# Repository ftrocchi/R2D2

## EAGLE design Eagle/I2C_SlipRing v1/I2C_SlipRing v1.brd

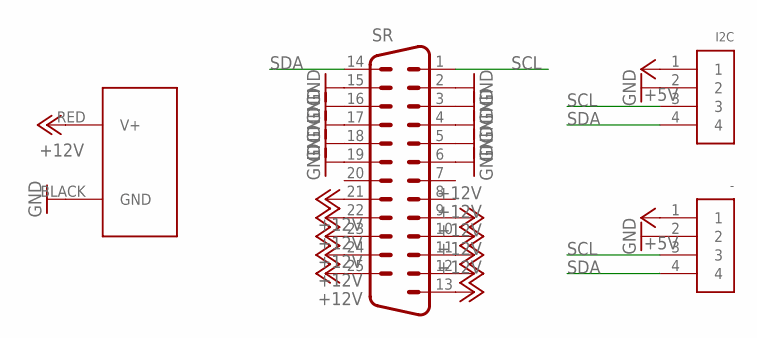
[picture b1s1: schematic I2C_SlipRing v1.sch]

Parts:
-: 1X4-CLEANBIG; 1X04-CLEANBIG
I2C: 1X4-CLEANBIG; 1X04-CLEANBIG
J1: POWERPOLE_POWER25A_HORIZONTAL_G2; POWERPOLE_PAIR_25A_HORIZ_G2
SR: DB25HP; M25HP

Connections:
+5V: -.1, I2C.1
+12V: J1.RED (V+), SR.9, SR.10, SR.11, SR.12, SR.13, SR.21, SR.22, SR.23, SR.24, SR.25
GND: -.2, I2C.2, J1.BLACK (GND), SR.2, SR.3, SR.4, SR.5, SR.6, SR.15, SR.16, SR.17, SR.18, SR.19
SCL: -.3, I2C.3, SR.1
SDA: -.4, I2C.4, SR.14

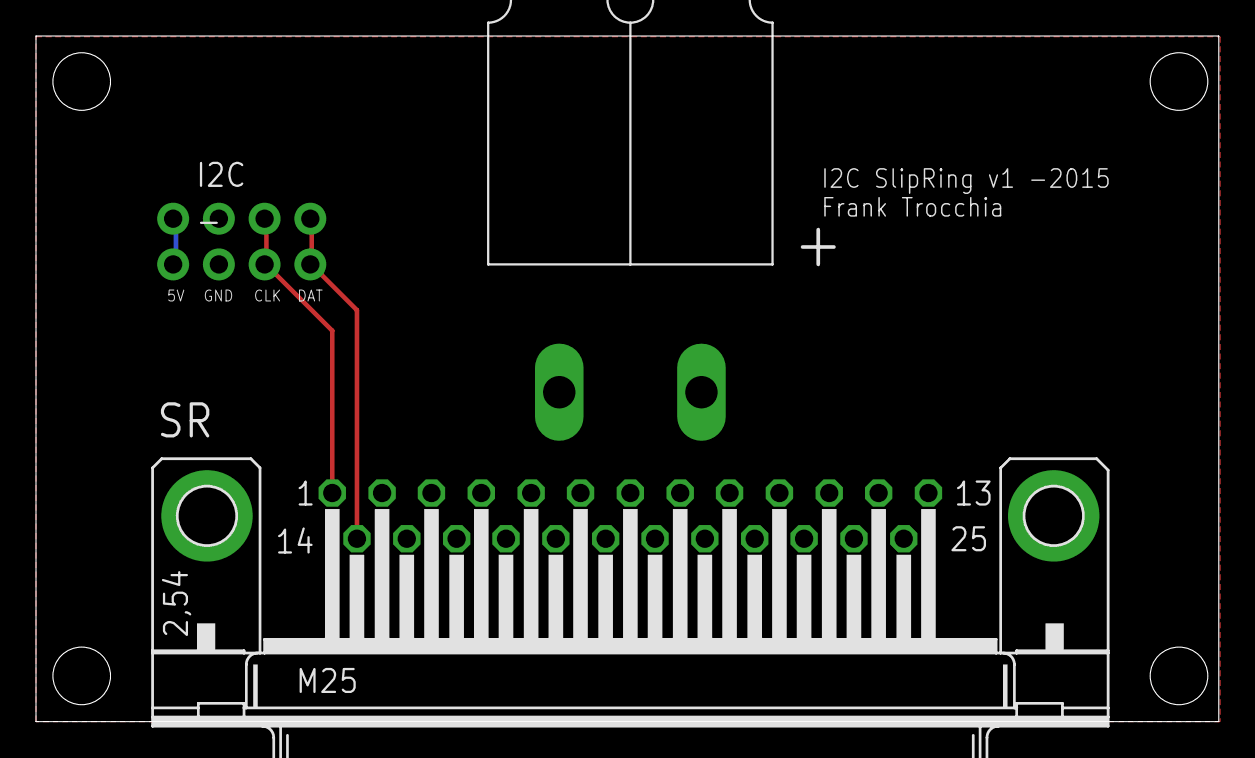
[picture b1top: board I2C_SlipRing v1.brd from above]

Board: 2 copper layers, 65.7 x 38.1 mm, 4 parts (0 on the bottom side), 5 nets.

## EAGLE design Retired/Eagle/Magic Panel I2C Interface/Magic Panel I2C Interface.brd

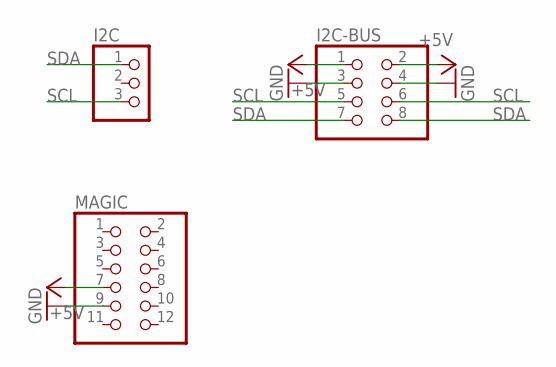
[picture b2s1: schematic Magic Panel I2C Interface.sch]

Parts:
I2C: PINHD-1X3CB; 1X03-CLEANBIG
I2C-BUS: PINHD-2X4; 2X04
MAGIC: PINHD-2X6; 2X06

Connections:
+5V: I2C-BUS.1, I2C-BUS.2, MAGIC.7
GND: I2C-BUS.3, I2C-BUS.4, MAGIC.9
SCL: I2C.3, I2C-BUS.5, I2C-BUS.6
SDA: I2C.1, I2C-BUS.7, I2C-BUS.8

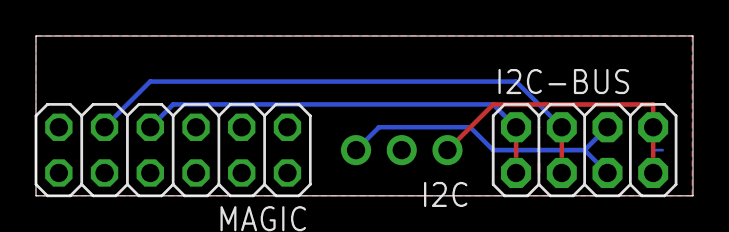
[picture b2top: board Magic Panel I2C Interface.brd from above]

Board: 2 copper layers, 36.5 x 8.9 mm, 3 parts (0 on the bottom side), 4 nets.

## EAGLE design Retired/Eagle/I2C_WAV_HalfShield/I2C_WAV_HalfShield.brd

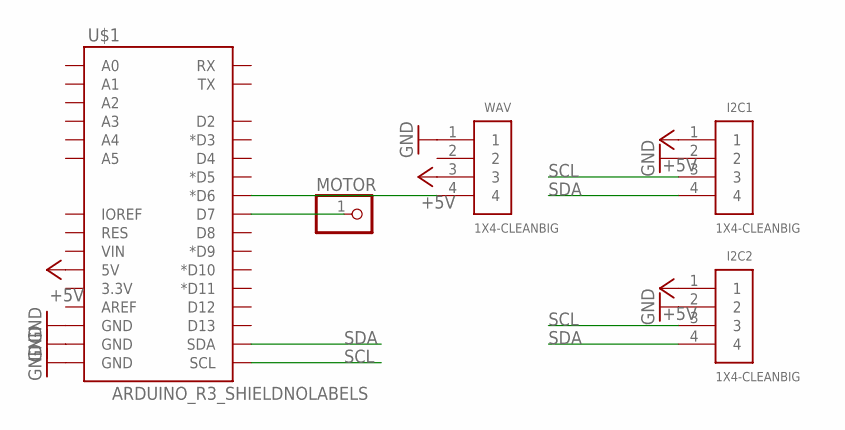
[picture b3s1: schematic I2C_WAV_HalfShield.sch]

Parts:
I2C1, I2C2: 1X4-CLEANBIG; 1X04-CLEANBIG
MOTOR: PINHD-1X1CB; 1X01-CLEANBIG
U$1: ARDUINO_R3_SHIELDNOLABELS; UNO_R3_SHIELD_NOLABELS
WAV: 1X4-CLEANBIG; 1X04-CLEANBIG

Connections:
+5V: I2C1.1, I2C2.1, U$1.5V, WAV.3
GND: I2C1.2, I2C2.2, U$1.GND@0 (GND), U$1.GND@1 (GND), U$1.GND@2 (GND), WAV.1
unnamed: MOTOR.1, U$1.D7
unnamed: U$1.D6 (*D6), WAV.4
SCL: I2C1.3, I2C2.3, U$1.SCL
SDA: I2C1.4, I2C2.4, U$1.SDA

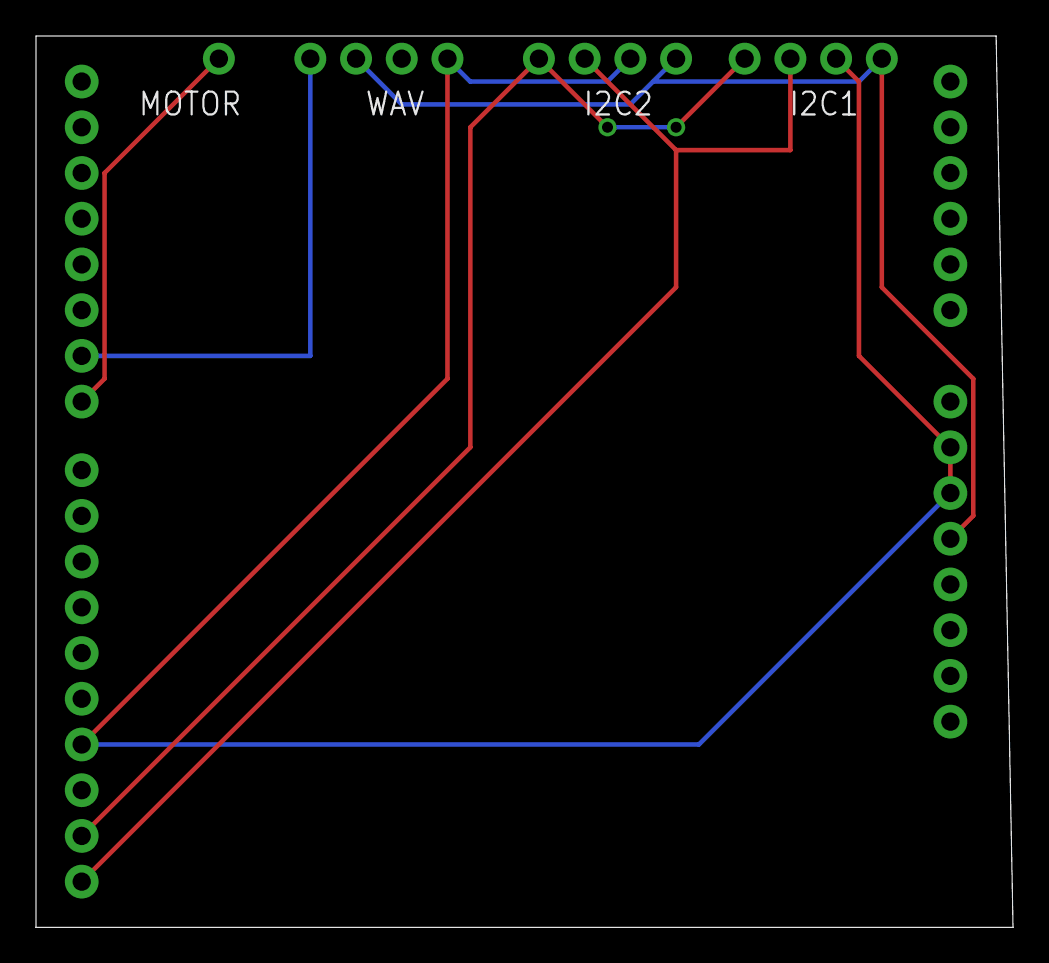
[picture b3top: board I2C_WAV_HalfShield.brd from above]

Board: 2 copper layers, 54.3 x 49.5 mm, 5 parts (0 on the bottom side), 6 nets.

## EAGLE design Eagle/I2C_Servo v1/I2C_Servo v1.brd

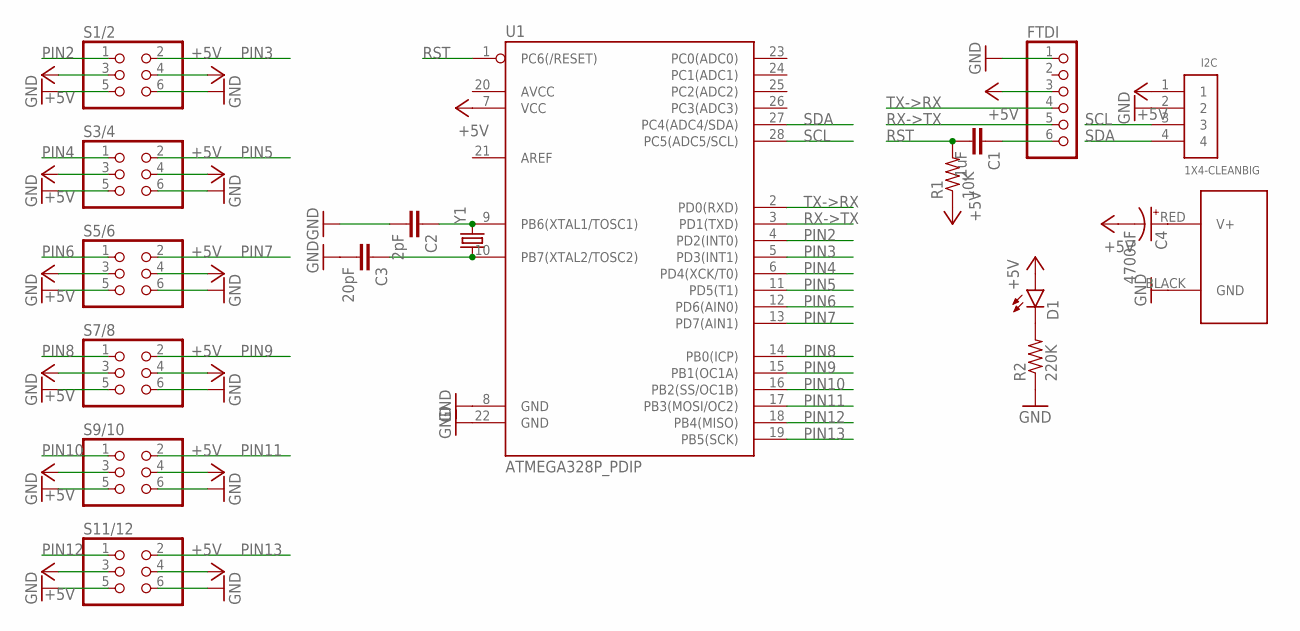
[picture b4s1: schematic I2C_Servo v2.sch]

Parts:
C1: .1uF; CAP-PTH-SMALL
C2: 2pF; CAP-PTH-SMALL
C3: 20pF; CAP-PTH-SMALL
C4: 4700uF; E5-13
D1: LED3MM
FTDI: PINHD-1X6CLEAN; 1X06-CLEAN
I2C: 1X4-CLEANBIG; 1X04-CLEANBIG
J1: POWERPOLE_POWER25A_HORIZONTAL_G2; POWERPOLE_PAIR_25A_HORIZ_G2
R1: 10K; AXIAL-0.3
R2: 220K; AXIAL-0.3
S1/2, S3/4, S5/6, S7/8, S9/10, S11/12: PINHD-2X3; 2X03
U1: ATMEGA328P_PDIP; DIL28-3
Y1: CRYSTALHC49US; HC49US

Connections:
+5V: C4.-, D1.A, FTDI.3, I2C.1, R1.P$1 (1), S1/2.3, S1/2.4, S3/4.3, S3/4.4, S5/6.3, S5/6.4, S7/8.3, S7/8.4, S9/10.3, S9/10.4, S11/12.3, S11/12.4, U1.7 (VCC)
GND: C2.2, C3.2, FTDI.1, I2C.2, J1.BLACK (GND), R2.P$1 (1), S1/2.5, S1/2.6, S3/4.5, S3/4.6, S5/6.5, S5/6.6, S7/8.5, S7/8.6, S9/10.5, S9/10.6, S11/12.5, S11/12.6, U1.8 (GND), U1.22 (GND)
unnamed: C1.1, FTDI.6
unnamed: C2.1, U1.9 (PB6(XTAL1/TOSC1)), Y1.2
unnamed: C3.1, U1.10 (PB7(XTAL2/TOSC2)), Y1.1
unnamed: C4.+, J1.RED (V+)
unnamed: D1.K (C), R2.P$2 (2)
PIN2: S1/2.1, U1.4 (PD2(INT0))
PIN3: S1/2.2, U1.5 (PD3(INT1))
PIN4: S3/4.1, U1.6 (PD4(XCK/T0))
PIN5: S3/4.2, U1.11 (PD5(T1))
PIN6: S5/6.1, U1.12 (PD6(AIN0))
PIN7: S5/6.2, U1.13 (PD7(AIN1))
PIN8: S7/8.1, U1.14 (PB0(ICP))
PIN9: S7/8.2, U1.15 (PB1(OC1A))
PIN10: S9/10.1, U1.16 (PB2(SS/OC1B))
PIN11: S9/10.2, U1.17 (PB3(MOSI/OC2))
PIN12: S11/12.1, U1.18 (PB4(MISO))
PIN13: S11/12.2, U1.19 (PB5(SCK))
RST: C1.2, R1.P$2 (2), U1.1 (PC6(/RESET))
RX->TX: FTDI.5, U1.3 (PD1(TXD))
SCL: I2C.3, U1.28 (PC5(ADC5/SCL))
SDA: I2C.4, U1.27 (PC4(ADC4/SDA))
TX->RX: FTDI.4, U1.2 (PD0(RXD))

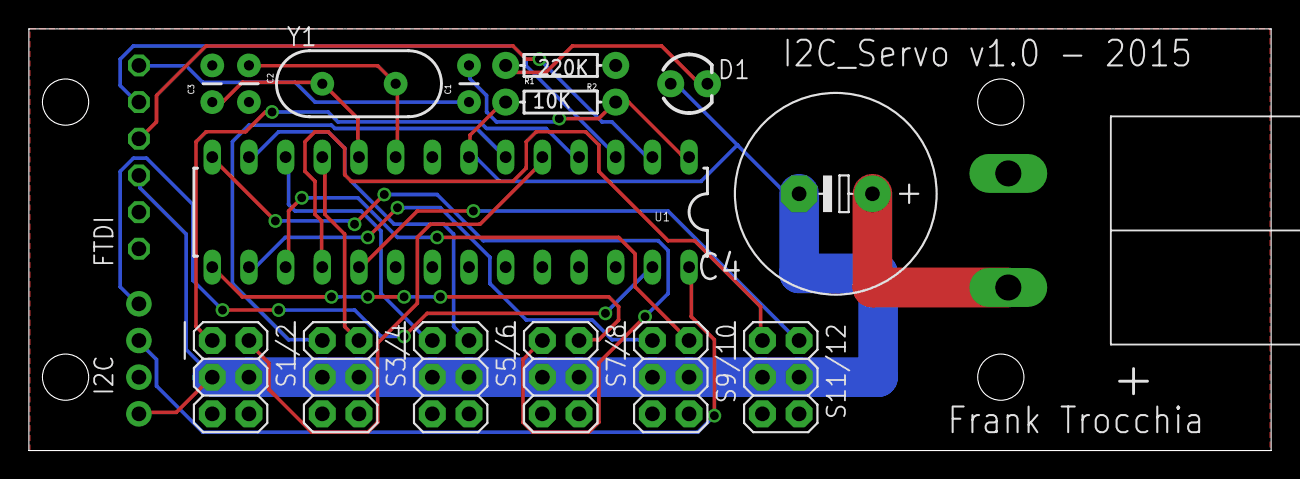
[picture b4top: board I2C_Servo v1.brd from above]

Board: 2 copper layers, 86.0 x 29.2 mm, 18 parts (0 on the bottom side), 24 nets.

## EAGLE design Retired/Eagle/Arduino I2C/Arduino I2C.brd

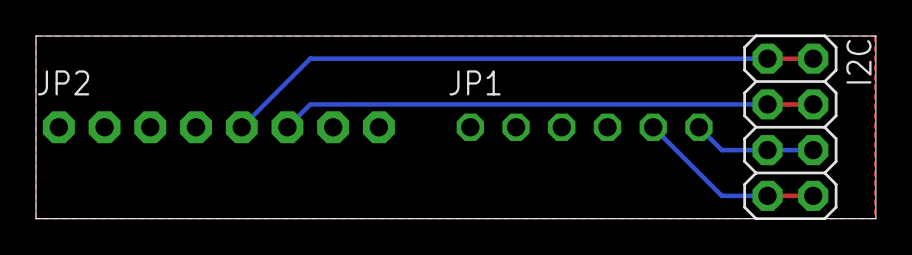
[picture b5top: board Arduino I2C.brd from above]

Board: 2 copper layers, 46.7 x 10.2 mm, 3 parts (0 on the bottom side), 4 nets.

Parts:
I2C: 2X04
JP1: 1X06-CLEAN
JP2: 1X08-CLEANBIG

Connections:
+5V: I2C.1, I2C.2, JP2.5
GND: I2C.3, I2C.4, JP2.6
SCL: I2C.5, I2C.6, JP1.6
SDA: I2C.7, I2C.8, JP1.5

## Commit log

2014-04-16 Added wiring diagrams previously created
2014-04-16 Added serial prints to each park method
2014-04-16 Adjusted pins to add motor controller pins.
    Added dropping the motor pin LOW when parking is required.
2014-04-17 Added the Arm
    Now can transmit and receive between the two devices!
2014-04-17 Fixed indents in override arm
2014-04-17 Added keypad arduino library
2014-04-17 Added xbee library
2014-04-17 added picture
2014-04-17 Added Sounds
2014-04-17 Changed directory name to be MP3 sounds
2014-04-17 Added WAV versions of body sounds
    Files haven't been listened to yet or tested with the WAV TRIGGER
2014-04-17 Removed images
2014-04-17 Added WAV Trigger software
2014-04-17 Added Dome Orientation Calculation Chart
2014-04-17 Added Dimension Engineering Docs
2014-04-17 Added SingleLED code
2014-04-19 Added PS2 controller code
2014-04-19 I2C_Master runs dome motor now
    Uses SendOnlySoftwareSerial. Also, added the sabertooth library
2014-04-19 Updated third party software index
2014-04-20 Added Sabertooth control
2014-04-21 First test of I2C_WAV
2014-04-21 Added some third party libraries
2014-04-22 Sync'd I2C_Common.h
2014-04-22 Removed startup sound
    Removed startup sound which should be placed in the main uno code.
    Cleaned up code also.
2014-04-22 Added startup sound. This is THX for now.
2014-04-22 Added command 8 b frame instructions
2014-04-22 Added file sync utility
    Moved source code around
2014-04-22 Updated WAV code for volume range
    volume range was -70 to +10. Mapped this to 0-255
2014-04-22 Updated code to play startup sound
    Needs tested
2014-04-22 Added other sounds in MP3 and WAV
2014-04-22 Changed wav and master to work together
2014-04-22 More audio changes
2014-04-23 Internediate changes for WAVTrigger
2014-04-23 All request only coded for WAVTrigger
    Needs testing
2014-05-02 Added domeplate image
2014-05-12 Began coding for new PS2 Shield
2014-05-13 Finished code changes for PS2
2014-05-13 Tweaks to PS2
2014-05-13 Lots of tweaks for PS2
2014-05-13 Tweaked the GetButtonBit method
2014-05-13 Retired old PS2 and updated I2C
2014-05-13 Put PS2 into main code
2014-05-15 tweaked GetButtonBit to return bool correctly
2014-05-18 Moved files around
    Main now runs audio as well. Retired WAV code.
2014-05-18 Added half shield
2014-05-25 Added WebSocket
2014-05-26 Added websocket library
2014-05-26 Added logging
2014-05-26 Updated PS2 controller for activity check
2014-05-26 Dual dome control working
2014-06-08 Audio changes
2014-06-08 Added website and volume controls
2014-06-09 Added volume control on tablet
2014-06-09 Common Master volume
2014-06-10 My changes
2014-06-11 Bug fixes
2014-06-26 Small changes after droidcon
2014-06-26 Added some eagle files
2014-06-28 Added start code for logics engine
2014-06-29 Added FastLED and other code. Stopping for the night.
2014-06-29 Added concept of modes
2014-06-29 Added idea of primary color
2014-06-29 Added March
2014-06-29 Added March Separate
2014-06-29 Modifed I2C for FLD / RLD
2014-06-29 Added march for RLD
2014-06-29 Changed to an independant model for displays
2014-06-29 March is now working
2014-06-29 March separate is now working
2014-06-30 Text is working.
2014-06-30 Added color shift, but must wait till evening to test.
2014-06-30 color shift tested
2014-06-30 Added freemem ability
2014-07-01 Added left, right, and leftright shifting
2014-07-01 Can change primary color now.
2014-07-06 Changes for RLD
2014-07-07 Added random pixel. Needs tested.
2014-07-07 Small changes to random pixel
2014-08-21 Started work on device specific code
2014-08-21 More minor changes
2014-08-26 Untested changes
2014-08-26 More untested changes
2014-08-27 Merge remote-tracking branch 'origin/master'
    Conflicts:
    Source Code/Arduino/Devices/HP/HP/HP.ino
    More work on the HP code
2014-08-27 Fixed merge issues
2014-08-27 Added system failure. Needs tested
2014-08-27 Verified changes. Now to work the servos.
2014-08-28 Now using analog write
2014-08-28 Initial Servo code
2014-08-28 More servo changes
2014-08-29 Added custom for servos, and cleaned up code
2014-08-29 Added test for custom servo movement
2014-08-31 HP Coding is finished.
2014-08-31 Added ethernet test website and tools
2014-09-01 Began work with 16 servo controller
2015-01-13 Updated Audio configuration
2015-02-15 Added panel stl file
2015-03-12 Corrected startup sound
2015-03-31 Retired everything to start fresh
2015-03-31 Added HP code
2015-03-31 Added Leia message and ability to shut off system events
2015-04-01 Code cleanup
2015-04-01 Added Imperial March event
    NOT YET TESTED
2015-04-01 Added SyncCommonFiles
    Moved folders around
2015-04-01 Added test code for Imperial March. Everything tested out.
2015-04-03 Updated times for Leia Message and Imperial March
2015-04-03 Imperial March temp is 103,
    though it changes faster and slower slightly
2015-04-03 Targetted Servo position works. Need more juice
    the ADK can provide.
2015-04-05 Removed Servo Code
2015-04-05 Fixed spacing
2015-04-05 Added Twitch Color
2015-04-06 Magic Panel
2015-04-07 Added eagle files
2015-04-07 Began coding servo logic
2015-04-07 More changes for servos
2015-04-07 More servo board code changes
2015-04-10 Began R2D2 Core
2015-07-17 small update
2015-09-02 Updated I2C Holo projector code

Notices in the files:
parts and their libraries:
SparkFun-Passives: Licensing: Creative Commons ShareAlike 4.0 International - https://creativecommons.org/licenses/by-sa/4.0
FJT-HALF_SHIELD: Licensing: CC v3.0 Share-Alike You are welcome to use this library for commercial purposes.
